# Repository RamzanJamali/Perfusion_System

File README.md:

# Pressure-Controlled Perfusion System

A modular, open-source pressure-controlled perfusion system designed for the biomechanical characterization of corneal tissue. This system provides precise control over retrocorneal pressure and perfusion flow rate for *ex vivo* experiments.

## 🚀 Quick Start

1.  **Hardware:** Assemble the mechanical components and connect the electronics as per the `hardware/` documentation.
2.  **Firmware:** Flash the Arduino with the appropriate controller firmware from the `Controller/` directory.
3.  **Software:** Install Python dependencies and run the recommended dashboard.
    ```bash
    pip install -r software/Dashboard_2/requirements.txt
    python software/Dashboard_2/app.py
    ```

## 📁 Repository Structure & Component Guide

Here is a breakdown of the key software components and their intended use:

| Component | Purpose | Recommendation |
| :--- | :--- | :--- |
| **`Controller/Controller_1`** | Firmware configured for the **Variohm CIT3100** pressure sensor. | Use if your hardware uses the CIT3100 sensor. |
| **`Controller/Controller_2`** | Firmware configured for the **Ceraphant PTC31B** pressure sensor. | **Recommended** for systems with the PTC31B sensor. |
| **`software/Dashboard_1`** | Legacy version of the Python control dashboard. | For reference or specific use cases. |
| **`software/Dashboard_2`** | Enhanced version with improved data visualization and control. | **Recommended** for all new installations. |

### 🔧 Hardware Specifications

Key components used in this system include:

*   **Stepper Motor Driver:** The TMC2209 driver module controls the NEMA 17 stepper motor, providing silent operation and advanced features like stealthChop2 for noiseless motion and spreadCycle for high-speed performance.
*   **Pressure Transducer:** The Ceraphant PTC31B is a pressure switch with a ceramic, vacuum-tight measuring cell, used for safe monitoring of absolute and gauge pressure. It is suitable for measurements in gases, vapors, and liquids.

## ⚙️ How to Use This Repository

### Downloading the Project

To get a copy of the project, you can **clone** the repository or **download it as a ZIP** file.

*   **Clone (recommended for development):**
    ```bash
    git clone https://github.com/RamzanJamali/Perfusion_System.git
    ```
*   **Download ZIP:**
    Click the `Code` button on the GitHub repository page and select "Download ZIP".

### Navigating the Code

- The `Controller/` directory contains the Arduino firmware. Select the version that matches your pressure sensor.
- The `software/` directory contains the Python-based dashboards. Use `Dashboard_2` for the best experience.
- Refer to the `hardware/` directory for assembly guides, CAD files, and the bill of materials.

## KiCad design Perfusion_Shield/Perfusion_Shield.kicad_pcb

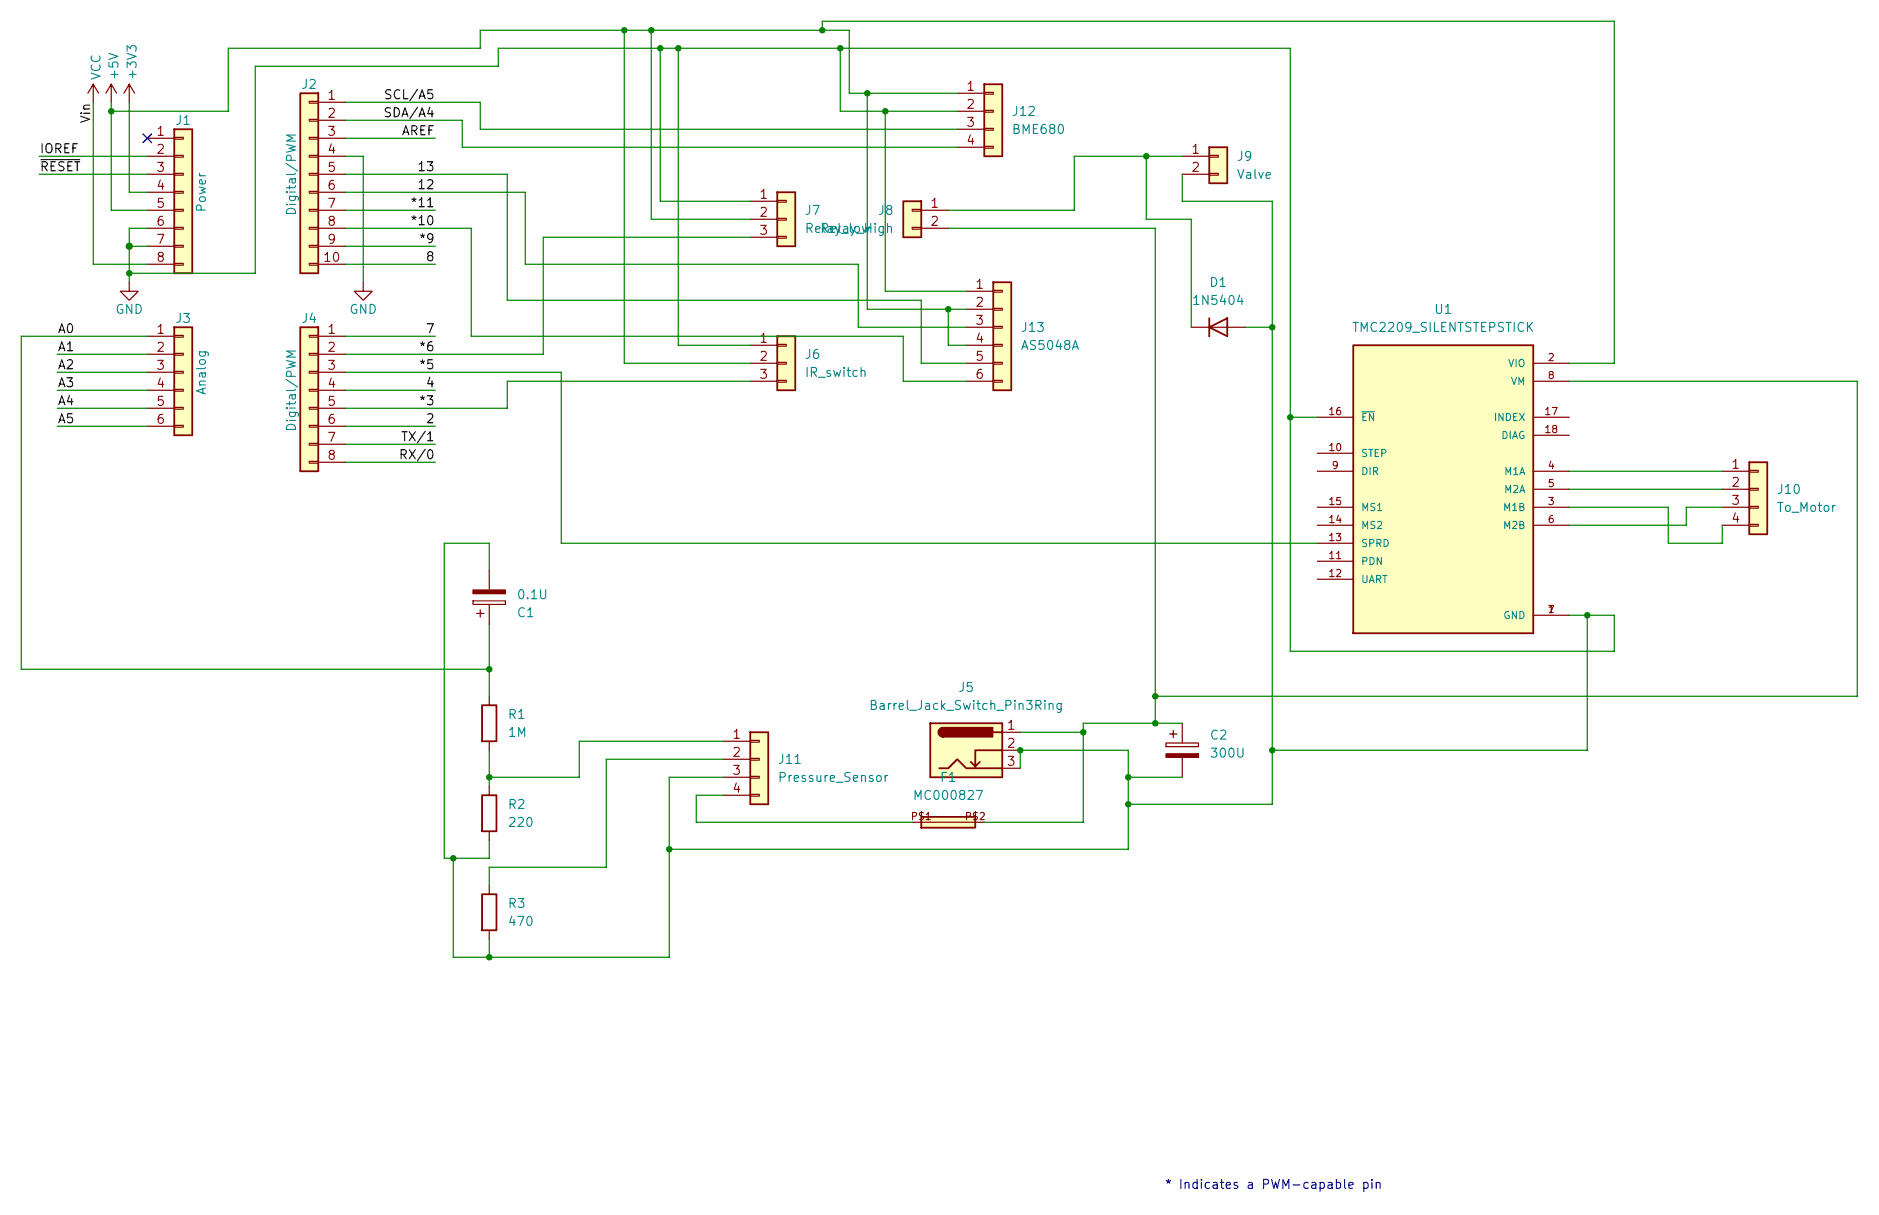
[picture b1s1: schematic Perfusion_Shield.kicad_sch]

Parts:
C1: 0.1U; C_Radial_D8.0mm_H7.0mm_P3.50mm
C2: 300U; C_Radial_D8.0mm_H11.5mm_P3.50mm
D1: 1N5404; D_DO-201AD_P15.24mm_Horizontal
F1: MC000827
J1: Power; PinHeader_1x08_P2.54mm_Vertical
J2: Digital/PWM; PinHeader_1x10_P2.54mm_Vertical
J3: Analog; PinHeader_1x06_P2.54mm_Vertical
J4: Digital/PWM; PinHeader_1x08_P2.54mm_Vertical
J5: Barrel_Jack_Switch_Pin3Ring; BarrelJack_GCT_DCJ200-10-A_Horizontal
J6: IR_switch; JST_XH_B3B-XH-A_1x03_P2.50mm_Vertical
J7: Relay_low; JST_XH_B3B-XH-A_1x03_P2.50mm_Vertical
J8: Relay_High; JST_XH_B2B-XH-A_1x02_P2.50mm_Vertical
J9: Valve; JST_XH_B2B-XH-A_1x02_P2.50mm_Vertical
J10: To_Motor; JST_XH_B4B-XH-A_1x04_P2.50mm_Vertical
J11: Pressure_Sensor; JST_XH_B4B-XH-A_1x04_P2.50mm_Vertical
J12: BME680; JST_XH_B4B-XH-A_1x04_P2.50mm_Vertical
J13: AS5048A; JST_XH_B6B-XH-A_1x06_P2.50mm_Vertical
R1: 1M; R_Axial_DIN0309_L9.0mm_D3.2mm_P12.70mm_Horizontal
R2: 220; R_Axial_DIN0309_L9.0mm_D3.2mm_P12.70mm_Horizontal
R3: 470; R_Axial_DIN0309_L9.0mm_D3.2mm_P12.70mm_Horizontal
U1: TMC2209_SILENTSTEPSTICK; MODULE_TMC2209_SILENTSTEPSTICK; PARTREV 1.20

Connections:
+3V3: J1.4
+5V: J1.5, J6.2, J7.2, J12.1, J13.2, J13.4, U1.2 (VIO)
/2: J4.6
/4: J4.4
/7: J4.1
/8: J2.10
/12: J2.6, J13.3
/13: J2.5, J13.5
/*3: J4.5, J6.3
/*5: J4.3, U1.13 (SPRD)
/*6: J4.2, J7.3
/*9: J2.9
/*10: J2.8, J13.6
/*11: J2.7
/A0: C1.1, J3.1, R1.1
/A1: J3.2
/A2: J3.3
/A3: J3.4
/A4: J3.5
/A5: J3.6
/AREF: J2.3
/IOREF: J1.2
/RX/0: J4.8
/SCL/A5: J2.1, J12.3
/SDA/A4: J2.2, J12.4
/TX/1: J4.7
/~RESET: J1.3
GND: C1.2, C2.2, D1.2 (A), J1.6, J1.7, J2.4, J5.2, J5.3, J6.1, J7.1, J9.2, J11.3, J12.2, J13.1, R2.2, R3.2, U1.1 (GND), U1.7 (GND), U1.16 (~EN)
unnamed: D1.1 (K), J8.1, J9.1
unnamed: C2.1, F1.P$2, J5.1, J8.2, U1.8 (VM)
unnamed: J10.1, U1.4 (M1A)
unnamed: J10.2, U1.5 (M2A)
unnamed: J10.3, U1.6 (M2B)
unnamed: J10.4, U1.3 (M1B)
unnamed: J11.1, R1.2, R2.1
unnamed: J11.2, R3.1
unnamed: F1.P$1, J11.4
VCC: J1.8

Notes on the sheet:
* Indicates a PWM-capable pin

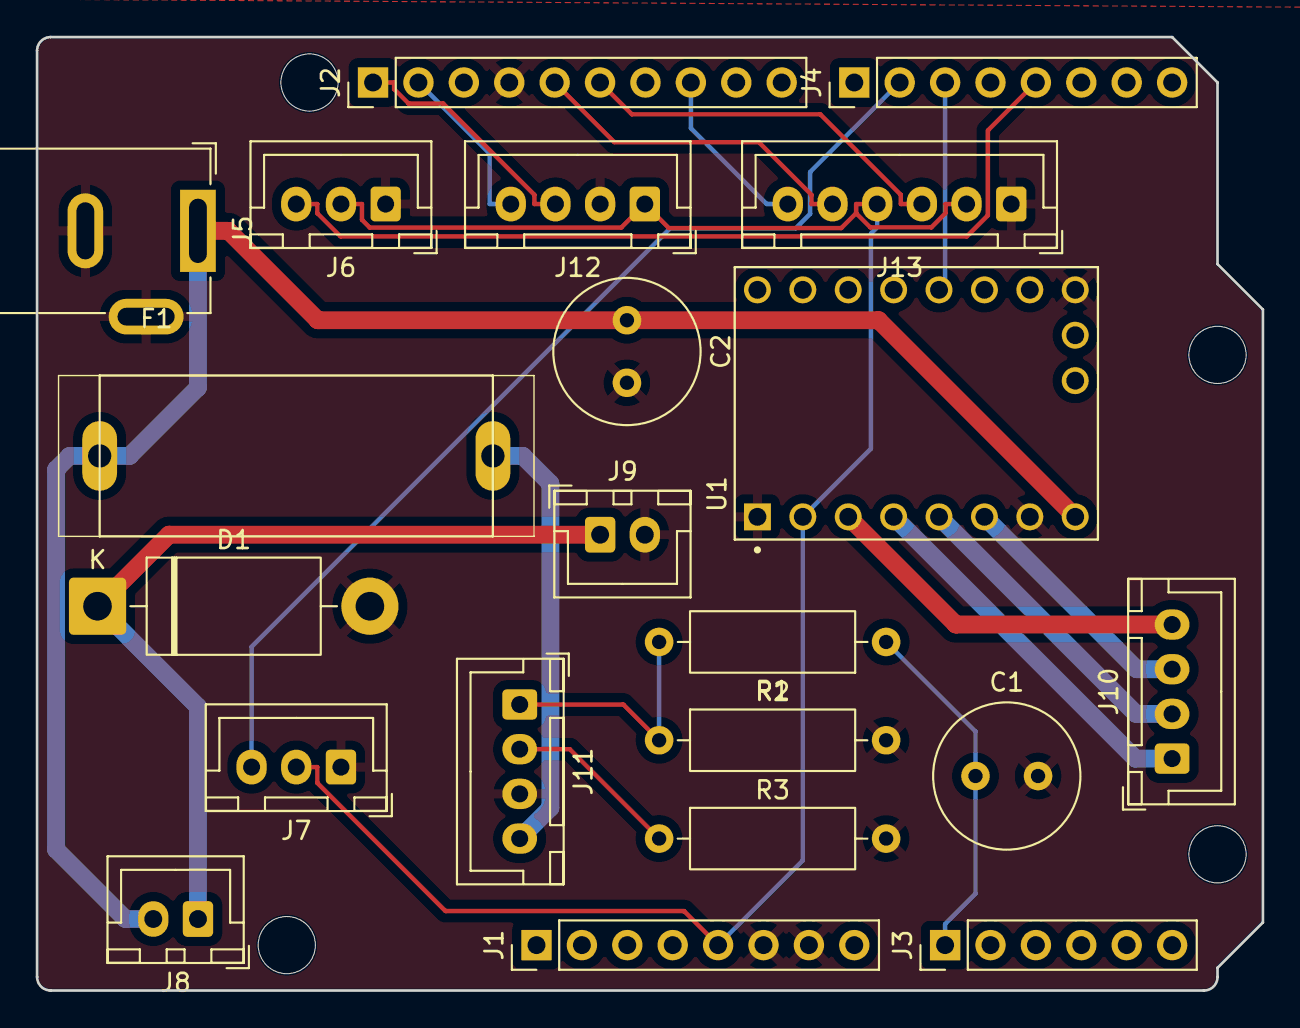
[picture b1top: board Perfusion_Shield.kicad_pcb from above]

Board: 2 copper layers, 68.6 x 53.3 mm, 25 parts (0 on the bottom side), 20 nets.

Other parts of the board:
MH1, MH2, MH3, MH4: MountingHole_3.2mm

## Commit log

2025-05-01 Adding files via upload from OneDrive
    Setting up the repository
2025-05-02 These files connect arduino with raspberry pi via usb cable
2025-05-02 File Upload 250502
2025-05-06 3D design files
    coupler, rod, stepper,syringe, etc
2025-05-06 3D files
    stepper, syringe, coupler, etc
2025-05-06 3D rod
    Threaded rod
2025-05-12 New files for motor driver added.
2025-05-12 New 3D files added to the repository. The files are ready for 3D printing and include the following formats: .ipt, .step, and .stl. The files are as follows: - Arduino base v12 - Barrel v11 - NemaMou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
2025-05-16 3D files and motor driver code Version 2 of the 3D files and motor driver code with accelstepper library is added.
2025-05-20 Added dashboard.py Added control panel for the stepper motor control with a GUI, it has three buttons to control the motor: run clockwise, run counterclockwise, and stop. It also displays the current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
2025-05-20 Added style to buttons in dashboard.py
2025-05-20 Added multiple drivers and removed unused files. Changed button style to be more consistent with the rest of the code. Removed extra files from the repository.
2025-05-21 Valve Control added. The following changes were made: - Added a new function to control the valve. - Integrated the valve control logic into the main loop. - Added a new button to the dashboard for m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
2025-05-22 Added New_connection.py and modified dashboard.py Added new experimental file named New_connection.py for testing new connection methods. Inserted some code in dashboard.py to test the new connection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
2025-05-22 Same as previous commit
2025-05-23 Added TMC2209 driver code and updated dashboard.py
2025-05-27 The TMC2209_driver code integrated with dashboard
2025-05-27 Added Temperature and Humidity Sensor to Arduino.
2025-05-27 Integrating SQLite
2025-05-28 Added classes to refactor code for Py and Arduino. Added save_data.py to save data into sqlite database. Added Perfusion class to handle perfusion logic. Added ReadTemperatureHumidity class to handle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
2025-05-28 Added code to handle commands in Controller.ino
2025-05-30 Implemented new dashboard and Uno libraries.
2025-06-03 Added new features to the Controller and Dashboard The Dashboard now set flow_rate in ml/min with minimum value of 1.7 ml/min. The Controller now operates on step per second instead of rpm and a new 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
2025-06-03 New feature: Add dashboard functionality Added a new @st.fragment decorated function to render log messages in the dashboard partially without refreshing the entire page.
2025-06-04 Model Sketch has been added A new model sketch has been created and added to the repository using Fritzing.
2025-06-04 Added encoder in sketch
2025-06-05 Added config.h, IR sensor and removed unused files config.h contains all the configuration parameters for the project. IR sensor is used to detect the position of the syringe pump at the end of the p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
2025-06-11 Added venv for raspberry Pi.
2025-06-11 Some miner fixes and updates
2025-06-11 some miner fixes
2025-06-11 New function added to select port automatically.
2025-06-11 Minor bug fix in dashboard.py
2025-06-12 Added code to save data only when perfusing. Added functionality to save data to a database when perfusing. Minor bug fixes and code cleanup.
2025-06-12 Added databases folder to save new db files. Added functionality to save data every time a perfusion is started. The data is saved accrording to the current date and time. Minor bug fixes in showing 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
2025-06-13 Added Pytest to test the dashboard.py Added Playwright to test the UI of the dashboard.py Added test_helpers.py to assist with testing
2025-06-16 Added AS5048A, updated Controller and Dashboard
    Added AS5048A library for angle sensing, updated Controller to integrate pressure sensing, and made changes to Dashboard for pressure sensor calibration.
2025-06-24 Added 3D files and AS5048A library Added 3D files for AS5048A mount and magnet holder, along with the AS5048A library files.
2025-06-24 Added 3D files and AS5048A library Added new Barrel 10ml file with holder for IR button. Added AS5048A library for rotary encoder support to the Controller file. Made changes to set motor based on AS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
2025-06-24 Added csv.py and run scripts for Pi and Windows Added csv.py file to database file into a CSV format. Added run scripts for Raspberry Pi and Windows to execute the csv.py and dashboard.py script.
2025-06-25 Added pressure sensor calibration to Controller Added pressure sensor calibration functionality to the Controller code. Fixed minor bugs in the Dashboard.
2025-06-25 Minor bug fixes and improvements Changed the port number for the dashboard and CSV run scripts to avoid conflicts with other services.
2025-06-25 Some minor bug fixes and improvements
2025-06-26 Added new functions to Controller and bug fixes Added speed_in_rpm to Controller, moved pressure functions to new Pressure header file Fixed bug with time in save_data.py converted speed to absolute 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
2025-06-26 Add path function according to Pi 4, Scalene added
2025-06-26 Changed read_db function to handle data with lists
2025-06-26 Minor bug fixes
2025-06-27 Modified Magnet_holder, bug fixes in dashboard.py
2025-06-27 minor bug fixes and performance improvements
2025-06-27 Added some comments to the config.h file
2025-07-01 minor bug fix
2025-07-01 Code formatted for clarity and maintainability. Code restructured to make it more readable and maintainable. Minor bug fixes and improvements to the logic.
2025-07-01 Changed speed_in_rpm and open_valve functions.
2025-07-02 Replaced AS5048A library with a new version.
2025-07-03 New function added to measure average speed.
2025-07-03 Minor bug fixes and speed calibaration
2025-07-03 New function added to measure motor speed
2025-07-03 New code to measure rpm
2025-07-09 Minor changes made to csv.py, added images of 3D
2025-07-11 Modified table loading Now table reads directly from the buffer instead of the database.
2025-07-11 Code reformatted and delay replaced. Reformatted the code to read all sensor data at the beginning of the loop. Replaced delay(1000) with if condition to check if the loop has run for at least 1000 m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
2025-07-11 New button to toggle valve state This commit adds a new button to the dashboard that allows users to toggle the valve state during IDLE mode.
2025-07-11 Minor bug fixes in Toggle Valve Button.
2025-07-14 New libraries for stepper motor and AS5048A added. Tested in new libraries and added formula for accurate flow rate calculation.
2025-07-15 Added AS5048A check program and RMP Formula New check program for AS5048A checks the distance between AS5048A and the magnet. RPM formula converts the RPM to the Microstepping period.
2025-07-15 Implementing new TMC library and bug fixes
2025-07-16 Added functionality to measure total NO. of Turns.
2025-07-16 Changed Perfusion library and minor bug fixes
2025-07-17 Test run fixes
2025-07-21 Modified print statements for loading time.
2025-07-22 Improved the measurements of the 3D models.
2025-07-24 New file added for BME680 Sensor Reading
2025-07-25 Perfusion Data Added
2025-07-25 New library added to separate TMC from Perfusion
2025-07-29 Separated TMC driver from Perfusion class.
2025-07-29 Minor bug fixes and refactoring
2025-07-29 Changes made in sensor data handling and dashboard New bme680 sensor is implemented and data structure is updated accordingly.
2025-07-30 New Excel sheet for measurements added
2025-07-31 Calculations changed for TMC controller
2025-07-31 More Measurements and formulas added.
2025-08-01 New reverse button functionality in the dashboard Reverse button added to the dashboard for adjusting syringe position. New Measurements added.
2025-08-06 Changed valve state reading functionality
2025-08-07 Changed the valve state reading
2025-08-07 Changed default values for perfusion
2025-08-08 New UI added to Dashboard_2
2025-08-11 Minor bug fixes and new Measurements added.
2025-08-11 New Waitress library included for production.
2025-08-13 New 3D files and Measurements added.
2025-08-13 Added .gitignore and removed venv from tracking
2025-08-13 Ignore venv directory
2025-08-13 Added script to run Pi_run_dashboard_2 on Pi 4.
2025-08-14 Added Measurements and updated TMC controller
2025-08-19 Minor bug fixes and code cleanup
2025-08-19 New pressure sensor added to the controller
2025-08-21 Add a measurement and changed speed in TMC.cpp
2025-08-21 Changed speed in TMC.cpp files
2025-08-25 Minor bug fixes in run scripts
2025-08-26 Added Measurements and minor bug fixes in Arduino
2025-08-29 Changed speed parameter and added a Measurement.
2025-09-03 Stop tracking Run folder
2025-09-03 Repository management
2025-09-03 added requirements.txt file
2025-09-04 New Measurements added
2025-09-08 New requirements.txt file added
2025-09-08 new requirements.txt added
2025-09-12 venv fixes
2025-09-16 New Measurements and 3D files for Gearbox added
2025-09-22 Output file name changed for CSV files
2025-09-22 Changed button colors by adding assets/style.css
2025-09-23 Speed parameter and valve safety threshold changed
2025-09-23 Time parameter changed for AS5048A Now time to measure the speed is set dynamically according to the speed of the motor
2025-09-23 Changed the speed parameter for TMC
2025-09-25 Speed parameter and reverse speed values changed
2025-09-26 New Measurements added and formula improved
2025-10-15 New PCB design files added for perfusion shield
2025-10-17 New Measurements added to the Excel file
2025-10-20 Perfusion CSV File
2025-10-20 Perfusion data file
2025-10-23 Screenshots added
2025-10-23 Images of New holder added.
2025-11-03 Deleted temporary files
2025-11-03 New README file added
2025-11-03 Made changes in README.md file.
2025-11-03 Renamed folder removed empty folders.
2025-12-04 New 3D files for Arduino Housing design added
